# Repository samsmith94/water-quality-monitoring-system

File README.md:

# Dokumentáció

## Kapcsolási rajz

## Websocket teszteléshez

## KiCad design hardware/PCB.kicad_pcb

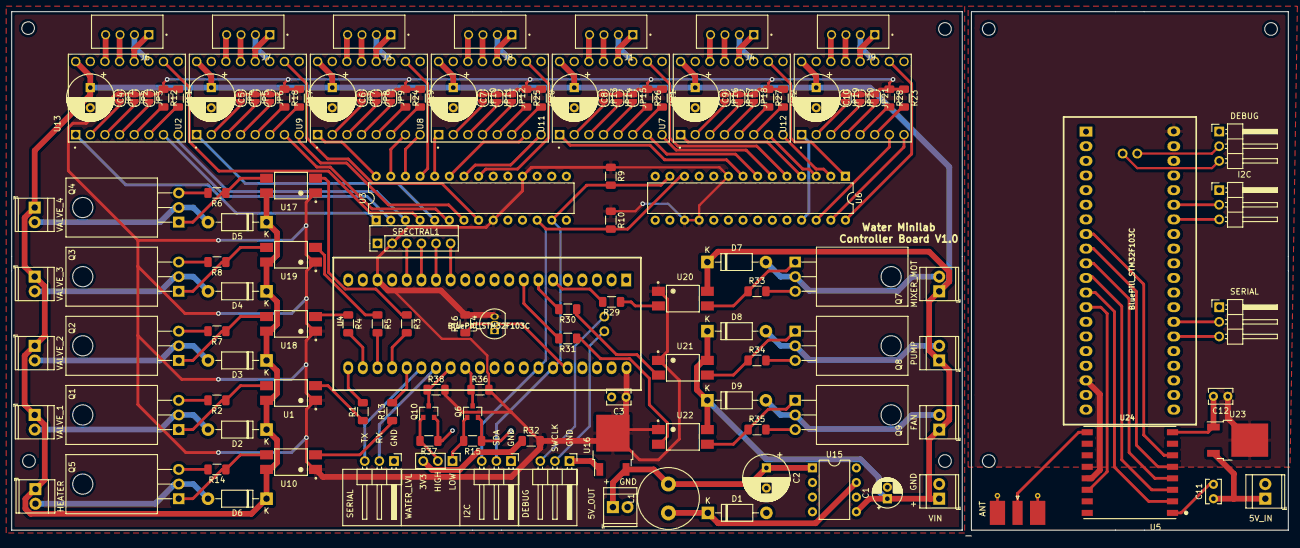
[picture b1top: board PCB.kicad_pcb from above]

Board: 2 copper layers, 221.6 x 91.0 mm, 149 parts (0 on the bottom side), 156 nets.

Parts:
5V_IN: 5_V_IN; TerminalBlock_TE_282834-2_1x02_P2.54mm_Horizontal
5V_OUT: 5_V_OUT; TerminalBlock_TE_282834-2_1x02_P2.54mm_Horizontal
ANT: Conn_Coaxial; SMA_Molex_73251-2120_EdgeMount_Horizontal
C1: 22uF; CP_Radial_D5.0mm_P2.00mm
C2: 220uF; CP_Radial_D8.0mm_P3.50mm
C3, C11, C12: 10uF; C_Rect_L4.0mm_W2.5mm_P2.50mm
C4, C5, C6, C7, C8, C9, C10: 100uF; CP_Radial_D8.0mm_P3.50mm
D1: 1N5818; D_DO-41_SOD81_P10.16mm_Horizontal
D2, D3, D4, D5, D6, D7, D8, D9: 1N4001; D_DO-41_SOD81_P10.16mm_Horizontal
DEBUG: DEBUG2; PinHeader_1x03_P2.54mm_Horizontal
DEBUG#2: DEBUG1; PinHeader_1x03_P2.54mm_Horizontal
FAN: Screw_Terminal_01x02; TerminalBlock_TE_282834-2_1x02_P2.54mm_Horizontal
H1, H2, H3, H4, H5, H6, H7: MountingHole; MountingHole_2.2mm_M2
HEATER: Screw_Terminal_01x02; TerminalBlock_TE_282834-2_1x02_P2.54mm_Horizontal
I2C, I2C#2: BLUEPILL_2; PinHeader_1x03_P2.54mm_Horizontal
J1, J3, J4, J6, J7, J8, J9: B4B-XH-A(LF)(SN); JST_B4B-XH-A(LF)(SN)
JP1, JP2, JP3, JP4, JP5, JP6, JP7, JP8, JP9, JP10, JP11, JP12, JP13, JP14, JP15, JP16, JP17, JP18, JP19, JP20, JP21: Jumper; SolderJumper-2_P1.3mm_Open_RoundedPad1.0x1.5mm
L1: INDUCTOR; L_Radial_D10.5mm_P5.00mm_Abacron_AISR-01
MIXER_MOT: Screw_Terminal_01x02; TerminalBlock_TE_282834-2_1x02_P2.54mm_Horizontal
PUMP: Screw_Terminal_01x02; TerminalBlock_TE_282834-2_1x02_P2.54mm_Horizontal
Q1, Q2, Q3, Q4, Q5, Q7, Q8, Q9: IRL540NSTRLPBF; TO-220-3_Horizontal_TabDown
Q6, Q10: BC847; SOT-23
R1, R3, R4, R5, R13, R29, R30, R31: 330R; R_1206_3216Metric_Pad1.30x1.75mm_HandSolder
R2, R6, R7, R8, R11, R12, R14, R17, R18, R19, R20, R21, R22, R23, R24, R25, R26, R27, R28, R33, R34, R35: 10k; R_1206_3216Metric_Pad1.30x1.75mm_HandSolder
R9, R10: 1k; R_1206_3216Metric_Pad1.30x1.75mm_HandSolder
R15, R37: 220k; R_1206_3216Metric_Pad1.30x1.75mm_HandSolder
R16: 4k7; R_1206_3216Metric_Pad1.30x1.75mm_HandSolder
R32: 22k; R_1206_3216Metric_Pad1.30x1.75mm_HandSolder
R36, R38: 470R; R_1206_3216Metric_Pad1.30x1.75mm_HandSolder
SERIAL: SERIAL2; PinHeader_1x03_P2.54mm_Horizontal
SERIAL#2: SERIAL1; PinHeader_1x03_P2.54mm_Horizontal
SPECTRAL1: Conn_01x06_Male; PinHeader_1x06_P2.54mm_Vertical
U1, U10, U17, U18, U19, U20, U21, U22: PC817X2NIP1B; SOT254P975X400-4N
U2, U7, U8, U9, U11, U12, U13: DRV8825_STEPPER_MOTOR_DRIVER_CARRIER; DRV8825-M
U3, U6: MCP23017_SP; DIP-28_W7.62mm
U4, U24: BluePill_STM32F103C
U5: RFM95W-868S2; XCVR_RFM95W-868S2
U14: DS18B20; TO-92_Inline
U15: LM2574HVN-5; DIP-8_W7.62mm
U16, U23: LM1117-3.3; TO-252-2
VALVE_1, VALVE_2, VALVE_3, VALVE_4: Screw_Terminal_01x02; TerminalBlock_TE_282834-2_1x02_P2.54mm_Horizontal
VIN: Screw_Terminal_01x02; TerminalBlock_TE_282834-2_1x02_P2.54mm_Horizontal
WATER_LVL: Conn_01x03; PinHeader_1x03_P2.54mm_Vertical

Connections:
5_V_IN: 5V_IN.1, C11.1, U23.3
5_V_OUT: 5V_OUT.1, C2.1, L1.2, U15.1, U16.3
+3V3: C3.1, C12.1, JP1.1, JP2.1, JP3.1, JP4.1, JP5.1, JP6.1, JP7.1, JP8.1, JP9.1, JP10.1, JP11.1, JP12.1, JP13.1, JP14.1, JP15.1, JP16.1, JP17.1, JP18.1, JP19.1, JP20.1, JP21.1, R9.1, R10.1, R11.1, R12.1, R16.2, R17.1, R18.1, R19.1, R20.1, R21.1, R22.1, R23.1, R24.1, R25.1, R26.1, R27.1, R28.1, R32.2, R36.2, R38.2, SPECTRAL1.2, U1.1, U3.9, U3.18, U4.18, U4.40, U5.13, U6.9, U6.17, U6.18, U10.1, U14.3, U16.2, U17.1, U18.1, U19.1, U20.1, U21.1, U22.1, U23.2, U24.18, U24.40
+12V: C1.1, C4.1, C5.1, C6.1, C7.1, C8.1, C9.1, C10.1, D2.1, D3.1, D4.1, D5.1, D6.1, D7.1, D8.1, D9.1, FAN.1, HEATER.1, MIXER_MOT.1, PUMP.1, U1.4, U2.16, U7.16, U8.16, U9.16, U10.4, U11.16, U12.16, U13.16, U15.5, U17.4, U18.4, U19.4, U20.4, U21.4, U22.4, VALVE_1.1, VALVE_2.1, VALVE_3.1, VALVE_4.1, VIN.1
DEBUG_UART_RX_1: SERIAL#2.2, U4.27
DEBUG_UART_RX_2: SERIAL.2, U24.27
DEBUG_UART_TX_1: SERIAL#2.3, U4.26
DEBUG_UART_TX_2: SERIAL.3, U24.26
FAN_PWM: R31.2, U4.8
GND: 5V_IN.2, 5V_OUT.2, ANT.2, C1.2, C2.2, C3.2, C4.2, C5.2, C6.2, C7.2, C8.2, C9.2, C10.2, C11.2, C12.2, D1.2, DEBUG.1, DEBUG#2.1, I2C.1, I2C#2.1, Q1.3, Q2.3, Q3.3, Q4.3, Q5.3, Q6.2, Q7.3, Q8.3, Q9.3, Q10.2, R2.2, R6.2, R7.2, R8.2, R14.2, R15.1, R33.2, R34.2, R35.2, R37.1, SERIAL.1, SERIAL#2.1, SPECTRAL1.1, U2.9, U2.15, U3.10, U3.15, U3.16, U3.17, U4.19, U4.20, U4.39, U5.1, U5.8, U5.10, U6.10, U6.15, U6.16, U7.9, U7.15, U8.9, U8.15, U9.9, U9.15, U11.9, U11.15, U12.9, U12.15, U13.9, U13.15, U14.1, U15.2, U15.3, U15.4, U16.1, U23.1, U24.19, U24.20, U24.39, VIN.2
I2C2_SCL: I2C.3, I2C#2.3, R10.2, U3.12, U4.34, U6.12, U24.34
I2C2_SDA: I2C.2, I2C#2.2, R9.2, U3.13, U4.35, U6.13, U24.35
LORA_DIO0_INT: U5.14, U24.13
LORA_MISO: U5.3, U24.11
LORA_MOSI: U5.2, U24.12
LORA_NSS: U5.5, U24.9
LORA_RESET: U5.6, U24.8
LORA_SCK: U5.4, U24.10
MIXER_MOTOR_PWM: R29.2, U4.6
unnamed: D1.1, L1.1, U15.7
unnamed: D2.2, Q1.2, VALVE_1.2
unnamed: D3.2, Q2.2, VALVE_2.2
unnamed: D4.2, Q3.2, VALVE_3.2
unnamed: D5.2, Q4.2, VALVE_4.2
unnamed: D6.2, HEATER.2, Q5.2
unnamed: D7.2, MIXER_MOT.2, Q7.2
unnamed: D8.2, PUMP.2, Q8.2
unnamed: D9.2, FAN.2, Q9.2
unnamed: ANT.1, U5.9
unnamed: JP1.2, U13.2
unnamed: JP2.2, U13.3
unnamed: JP3.2, U13.4
unnamed: JP4.2, U2.2
unnamed: JP5.2, U2.3
unnamed: JP6.2, U2.4
unnamed: JP7.2, U9.2
unnamed: JP8.2, U9.3
unnamed: JP9.2, U9.4
unnamed: JP10.2, U8.2
unnamed: JP11.2, U8.3
unnamed: JP12.2, U8.4
unnamed: JP13.2, U11.2
unnamed: JP14.2, U11.3
unnamed: JP15.2, U11.4
unnamed: JP16.2, U7.2
unnamed: JP17.2, U7.3
unnamed: JP18.2, U7.4
unnamed: JP19.2, U12.2
unnamed: JP20.2, U12.3
unnamed: JP21.2, U12.4
unnamed: Q1.1, R2.1, U1.3
unnamed: Q2.1, R7.1, U18.3
unnamed: Q3.1, R8.1, U19.3
unnamed: Q4.1, R6.1, U17.3
unnamed: Q5.1, R14.1, U10.3
unnamed: Q6.1, R15.2, WATER_LVL.1
unnamed: Q7.1, R33.1, U20.3
unnamed: Q8.1, R34.1, U21.3
unnamed: Q9.1, R35.1, U22.3
unnamed: Q10.1, R37.2, WATER_LVL.2
unnamed: R1.1, U1.2
unnamed: R3.1, U17.2
unnamed: R4.1, U18.2
unnamed: R5.1, U19.2
unnamed: R11.2, U13.6
unnamed: R12.2, U13.5
unnamed: R13.1, U10.2
unnamed: R17.2, U2.6
unnamed: R18.2, U2.5
unnamed: R19.2, U9.6
unnamed: R20.2, U8.6
unnamed: R21.2, U11.6
unnamed: R22.2, U7.6
unnamed: R23.2, U12.6
unnamed: R24.2, U9.5
unnamed: R25.2, U8.5
unnamed: R26.2, U11.5
unnamed: R27.2, U7.5
unnamed: R28.2, U12.5
unnamed: R29.1, U20.2
unnamed: R30.1, U21.2
unnamed: R31.1, U22.2
unnamed: R32.1, WATER_LVL.3
PELTIER: R13.2, U4.25
PUMP_PWM: R30.2, U4.7
SPECTRAL_I2C_INT: SPECTRAL1.5, U4.14
SPECTRAL_I2C_RST: SPECTRAL1.6, U4.13
SPECTRAL_I2C_SCL: SPECTRAL1.4, U4.15
SPECTRAL_I2C_SDA: SPECTRAL1.3, U4.16
STEPPER_MOT1_A1: J6.1, U13.12
STEPPER_MOT1_A2: J6.2, U13.11
STEPPER_MOT1_B1: J6.3, U13.13
STEPPER_MOT1_B2: J6.4, U13.14
STEPPER_MOT1_DIR: U3.3, U13.8
STEPPER_MOT1_EN: U3.1, U13.1
STEPPER_MOT1_FLT: U3.4, U13.10
STEPPER_MOT1_STEP: U3.2, U13.7
STEPPER_MOT2_A1: J7.1, U2.12
STEPPER_MOT2_A2: J7.2, U2.11
STEPPER_MOT2_B1: J7.3, U2.13
STEPPER_MOT2_B2: J7.4, U2.14
STEPPER_MOT2_DIR: U2.8, U3.7
STEPPER_MOT2_EN: U2.1, U3.5
STEPPER_MOT2_FLT: U2.10, U3.8
STEPPER_MOT2_STEP: U2.7, U3.6
STEPPER_MOT3_A1: J3.1, U9.12
STEPPER_MOT3_A2: J3.2, U9.11
STEPPER_MOT3_B1: J3.3, U9.13
STEPPER_MOT3_B2: J3.4, U9.14
STEPPER_MOT3_DIR: U3.26, U9.8
STEPPER_MOT3_EN: U3.28, U9.1
STEPPER_MOT3_FLT: U3.25, U9.10
STEPPER_MOT3_STEP: U3.27, U9.7
STEPPER_MOT4_A1: J8.1, U8.12
STEPPER_MOT4_A2: J8.2, U8.11
STEPPER_MOT4_B1: J8.3, U8.13
STEPPER_MOT4_B2: J8.4, U8.14
STEPPER_MOT4_DIR: U3.22, U8.8
STEPPER_MOT4_EN: U3.24, U8.1
STEPPER_MOT4_FLT: U3.21, U8.10
STEPPER_MOT4_STEP: U3.23, U8.7
STEPPER_MOT5_A1: J1.1, U11.12
STEPPER_MOT5_A2: J1.2, U11.11
STEPPER_MOT5_B1: J1.3, U11.13
STEPPER_MOT5_B2: J1.4, U11.14
STEPPER_MOT5_DIR: U6.6, U11.8
STEPPER_MOT5_EN: U6.8, U11.1
STEPPER_MOT5_FLT: U6.5, U11.10
STEPPER_MOT5_STEP: U6.7, U11.7
STEPPER_MOT6_A1: J4.1, U7.12
STEPPER_MOT6_A2: J4.2, U7.11
STEPPER_MOT6_B1: J4.3, U7.13
STEPPER_MOT6_B2: J4.4, U7.14
STEPPER_MOT6_DIR: U6.2, U7.8
STEPPER_MOT6_EN: U6.4, U7.1
STEPPER_MOT6_FLT: U6.1, U7.10
STEPPER_MOT6_STEP: U6.3, U7.7
STEPPER_MOT7_A1: J9.1, U12.12
STEPPER_MOT7_A2: J9.2, U12.11
STEPPER_MOT7_B1: J9.3, U12.13
STEPPER_MOT7_B2: J9.4, U12.14
STEPPER_MOT7_DIR: U6.27, U12.8
STEPPER_MOT7_EN: U6.25, U12.1
STEPPER_MOT7_FLT: U6.28, U12.10
STEPPER_MOT7_STEP: U6.26, U12.7
SWCLK_1: DEBUG#2.2, U4.41
SWCLK_2: DEBUG.2, U24.41
SWDIO_1: DEBUG#2.3, U4.42
SWDIO_2: DEBUG.3, U24.42
TEMPERATURE: R16.1, U4.36, U14.2
VALVE_1: R1.2, U4.21
VALVE_2: R4.2, U4.22
VALVE_3: R5.2, U4.23
VALVE_4: R3.2, U4.24
WATER_HIGH_LEVEL: Q10.3, R38.1, U4.28
WATER_LOW_LEVEL: Q6.3, R36.1, U4.29

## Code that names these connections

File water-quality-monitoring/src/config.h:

//nem kell irányt állítani setup-ban
#define TEMPERATURE_PIN         PB8

//szintén nem kell az i2c lábakhoz sem irányt állítani

// OUTPUT
#define USER_LED_PIN            PC13

//EZ LENNE A NYÁK SZERINT:
//#define MIXER_MOTOR_PIN         PA1     //nem működik
//#define PUMP_PWM_PIN            PA2     //működik, de az irányváltás miatt ez legyen a mixer inkább
//#define FAN_PWM_PIN             PA3     //EZ LESZ A MIXER (A FAN MEHETNE A H-HÍD MÁSIK KIMENETÉRE...)

//DE ÁT KELL DEFÍNIÁLNI, MERT AZ ELSŐ NEM MŰKÖDIK SAJNOS

#define MIXER_MOTOR_PIN         PA2
#define PUMP_PWM_PIN            PB0

// H-híd irányállító lábak
#define IN1 PB10
#define IN2 PB1

#define PELTIER_PIN             PA8
#define VALVE_1_PIN             PB12
#define VALVE_2_PIN             PB13
#define VALVE_3_PIN             PB14
#define VALVE_4_PIN             PB15

// INPUT
#define WATER_LOW_LEVEL_PIN     PA12
#define WATER_HIGH_LEVEL_PIN    PA11

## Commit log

2021-02-22 reinit git
